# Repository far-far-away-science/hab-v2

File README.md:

# HAB Version II

Code and hardware designs for a high altitude balloon, the second version of https://github.com/far-far-away-science/hab . This version switches to a more efficient STM32L0 processor, adds support for a backup radio using LoRA, and hopes to include additional sensors.

Different licenses may apply to subsections of this repository. See the appropriate LICENSE files in the desired subdirectories.

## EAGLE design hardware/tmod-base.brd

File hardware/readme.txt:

all hardware designs, PCBs, schematics, drawings, specs go into this folder

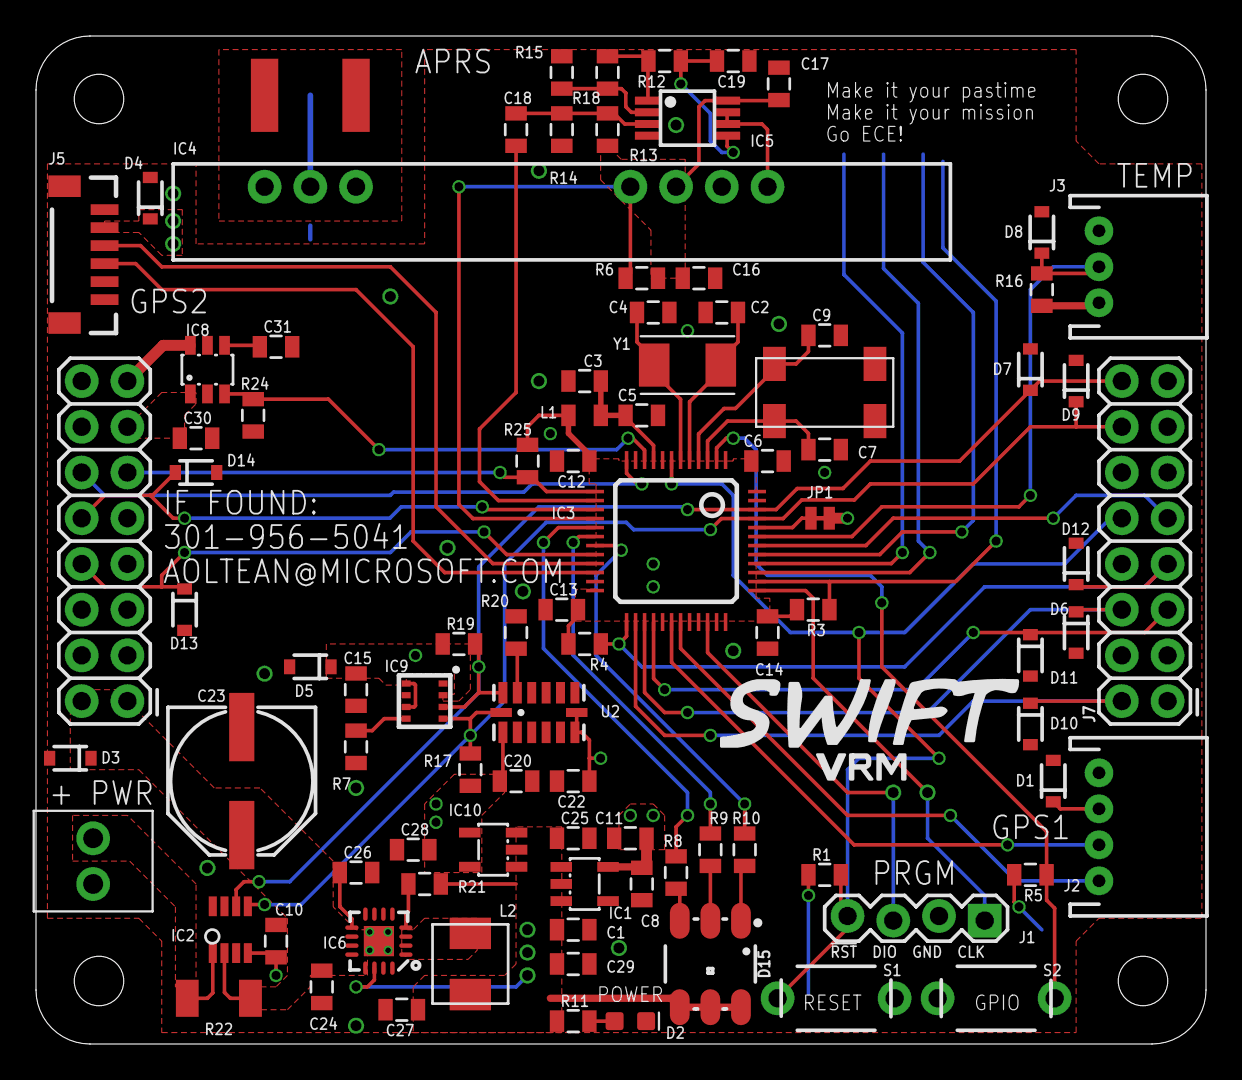
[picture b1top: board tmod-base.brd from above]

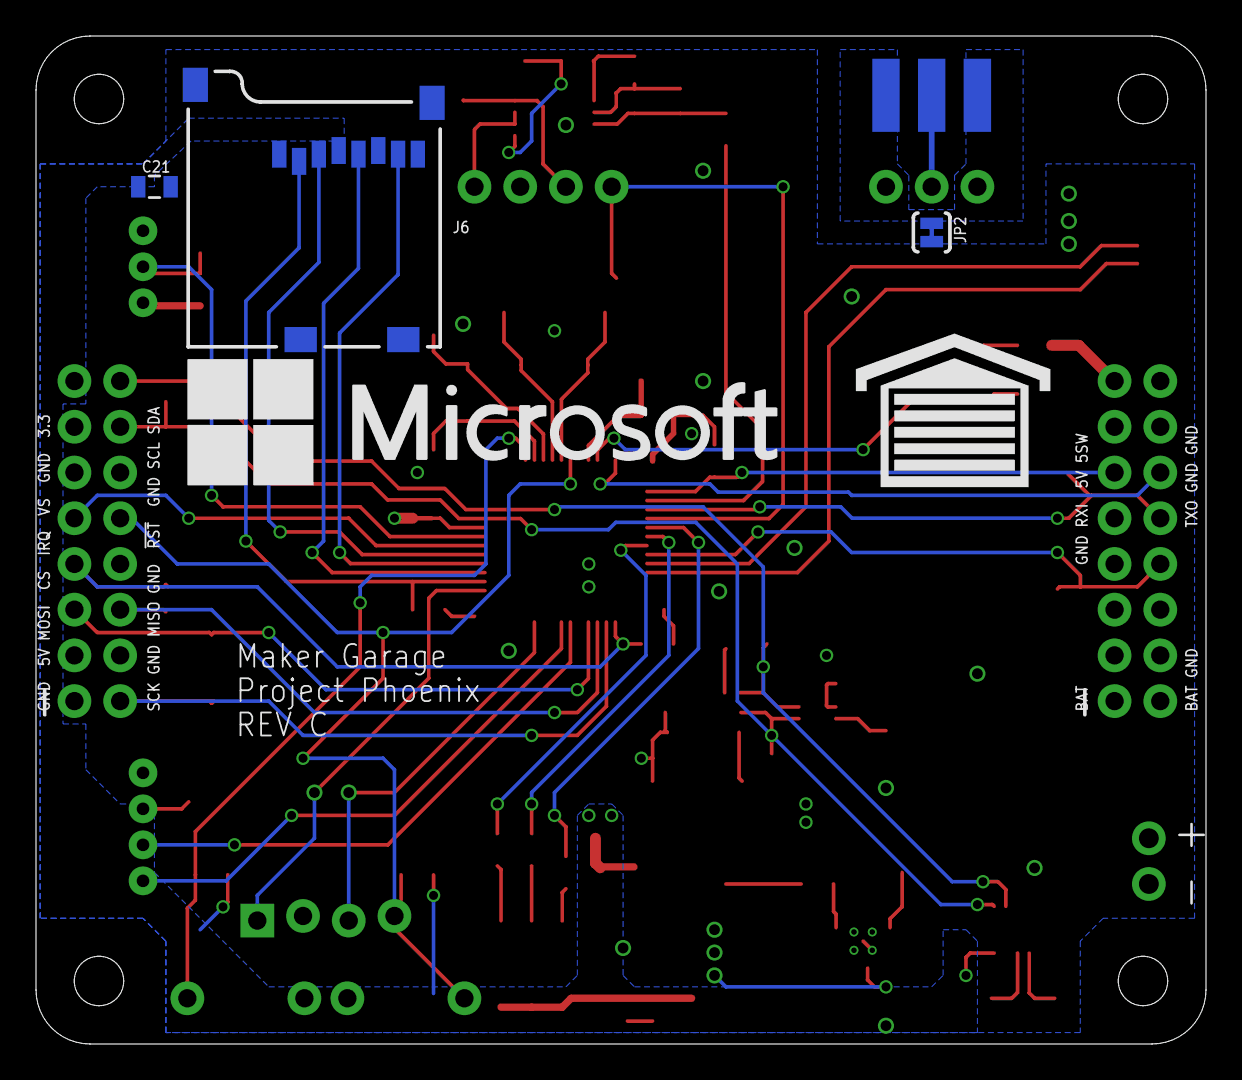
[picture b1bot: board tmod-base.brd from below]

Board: 4 copper layers, 65.0 x 56.0 mm, 100 parts (6 on the bottom side), 60 nets.

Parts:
C1, C5, C6, C10, C12, C13, C14, C15, C17, C22, C25, C30: 0.1u; 0805
C2, C4: 33p; 0805
C3, C8, C16, C21, C24, C28: 1u; 0805
C7, C9: 10p; 0805
C11, C27, C29: 10u; 0805
C18: 330p; 0805
C19: 100p; 0805
C20: 1.0u; 0805
C23: 150u; PANASONIC_E
C26: 3.3n; 0805
C31: 1n; 0805
D1, D4, D5, D6, D7, D8, D9, D10, D11, D12, D13, D14: 5.6V; SOD-323
D2: POWER; LED-0603
D3: 15V; SOD-323
D15: LED-RGB; LED-TRICOLOR-5050
FRAME1, FRAME2: FRAME-LETTERNO_PACKAGE; DUMMY
IC1, IC10: TPS70933; SOT23-DBV
IC2: INA219SOT; SOT23-8
IC3: STM32L443CCT6; TQFP48
IC4: HX1
IC5: LMP7702; VSSOP8
IC6: TPS62143; QFN16-3X3MM
IC8: TPS22918; SOT23-6L
IC9: BME280; BME280_LGA
J1: DNP; 1X04_LOCK@1
J2: GPS1; JST-4-PTH
J3: TEMP; JST-3-PTH
J4: POWER; 1X02_SCREW
J5: GPS2; 1X06-1MM
J6: MICRO-SD_CARD_SOCKET; MICRO-SD-SOCKET
J7: HAB-EXP
J$1: SMA_EDGE; SMA-EDGE
JP1: SMT-JUMPER_2_NC_TRACE_NO-SILK
JP2: GND; PAD-JUMPER-2-NC_BY_TRACE_YES_SILK
L1: FERRITE; 0805
L2: 2.2u; MPIA4012V2
R1, R3, R4, R5, R7, R20, R24, R25: 10K; 0805
R6, R16: 4.7K; 0805
R8, R9: 470; 0805
R10: 560; 0805
R11, R17, R19: 3.3K; 0805
R12: 330K; 0805
R13: 820K; 0805
R14: 220K; 0805
R15: 430K; 0805
R18: 680K; 0805
R21: 100K; 0805
R22: 0.01; 1210
S1: RST; TACTILE-PTH-THIN
S2: BTN; TACTILE-PTH-THIN
U2: ADXL345; LGA14
U$1: MSFT_LOGO
U$2: GARAGE
U$3: SWIFT
Y1: 8M; CRYSTAL-TXC-7A
Y2: 32768; ABS25

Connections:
3.3V: C6.1, C8.1, C10.1, C11.1, C12.1, C13.1, C14.1, C21.1, D1.C, IC1.5, IC2.4, IC3.1, IC3.24, IC3.36, IC3.48, J2.2, J6.VCC, J7.B15, L1.1, R1.2, R3.2, R4.2, R5.2, R25.2
5V: C1.1, C16.1, C17.1, C25.1, C27.1, C29.1, C30.1, D4.C, D15.4, D15.5, D15.6, IC1.1, IC4.5, IC5.8, IC6.14, IC8.1, IC10.1, J5.2, J7.A13, J7.B3, L2.2, R6.2, R11.1, R13.2, R21.2
5V_PI: IC8.6, J7.A15
!RST!: IC3.7, J1.4, J7.B10, R1.1, S1.2
A+: C18.2, IC5.3, R13.1, R14.2
A-: IC5.2, R15.2, R18.1
ADXL_SDO: R20.2, U2.12
BC: D15.1, R10.2
BME_SDO: IC9.P$5, R7.2
BOOT0: IC3.44, JP1.1
BTN: IC3.2, R5.1, S2.2
CT: C31.1, IC8.4
DAC: C18.1, IC3.14
GC: D15.2, R9.2
GND: C1.2, C2.2, C3.2, C4.2, C5.2, C6.2, C7.2, C8.2, C9.2, C10.2, C11.2, C12.2, C13.2, C14.2, C15.2, C16.2, C17.2, C19.2, C20.2, C21.2, C22.2, C23.-, C24.2, C25.2, C26.2, C27.2, C28.2, C29.2, C30.2, C31.2, D1.A, D2.C, D3.A, D4.A, D5.A, D6.A, D7.A, D8.A, D9.A, D10.A, D11.A, D12.A, D13.A, D14.A, IC1.2, IC2.3, IC2.7, IC2.8, IC3.8, IC3.23, IC3.35, IC3.47, IC4.6, IC5.4, IC6.5, IC6.6, IC6.7, IC6.8, IC6.15, IC6.16, IC6.EXT, IC8.2, IC9.P$1, IC9.P$7, IC10.2, J1.2, J2.1, J3.1, J4.2, J5.1, J5.5, J6.GND, J6.GND1, J6.GND3, J7.A4, J7.A9, J7.A14, J7.A16, J7.B1, J7.B4, J7.B8, J7.B12, J7.B13, JP1.2, JP2.2, R7.1, R14.1, R15.1, R20.1, R24.2, S1.1, S2.1, U2.2, U2.4, U2.5
GPSRX1: IC3.31, J2.4
GPSRX2: IC3.22, J5.4
GPSTX1: IC3.30, J2.3
GPSTX2: IC3.21, J5.3
HXEN: IC3.16, IC4.4, R6.1
K_PI: IC3.10, IC8.3, R24.1
LCS: D12.C, IC3.25, J7.B7, R4.1
LEDB: IC3.19, R10.1
LEDG: IC3.18, R9.1
LEDR: IC3.17, R8.1
LP1: IC5.1, R12.1, R18.2
LP2: C19.1, IC5.5, R12.2
MISO1: IC3.40, J6.DO
MISO2: D6.C, IC3.27, J7.B6
MOSI1: IC3.41, J6.DI
MOSI2: D11.C, IC3.28, J7.B5
OSC32_IN: C7.1, IC3.3, Y2.1
OSC32_OUT: C9.1, IC3.4, Y2.4
OSC_IN: C2.1, IC3.5, Y1.P$1
OSC_OUT: C4.1, IC3.6, Y1.P$2
PG5: IC6.4, R21.1
PLED: D2.A, R11.2
RC: D15.3, R8.2
RF_HX1: IC4.2, J$1.SIG
RGND: IC4.1, IC4.3, J$1.GND@0, J$1.GND@1, J$1.GND@2, J$1.GND@3, JP2.1
RSV5: D13.C, IC3.20, J7.A8
RSV6: D14.C, IC3.15, J7.A10
RSV7: IC3.42, J7.B9
R_RX: IC3.13, J7.A11, R25.1
R_TX: IC3.12, J7.A12
SCK1: IC3.39, J6.SCLK
SCK2: D10.C, IC3.26, J7.B2
SCL: D9.C, IC2.5, IC3.45, IC9.P$4, J7.B14, R17.1, U2.14
SDA: D7.C, IC2.6, IC3.46, IC9.P$3, J7.B16, R19.1, U2.13
SDCS: IC3.38, J6.CS, R3.1
SS5: C26.1, IC6.9
SW5: IC6.1, IC6.2, IC6.3, L2.1
SWCLK: IC3.37, J1.1
SWDIO: IC3.34, J1.3
TEMP: D8.C, IC3.43, J3.2, R16.1
TXD: IC4.7, IC5.6, IC5.7
VBAT: C23.+, C24.1, D3.C, IC2.2, IC6.10, IC6.11, IC6.12, IC6.13, J7.A1, J7.A2, R22.1
VDDA: C3.1, C5.1, IC3.9, L1.2
VIN: IC2.1, J4.1, R22.2
VS: C15.1, C20.1, C22.1, C28.1, D5.C, IC9.P$2, IC9.P$6, IC9.P$8, IC10.5, J3.3, J7.B11, R16.2, R17.2, R19.2, U2.1, U2.6, U2.7

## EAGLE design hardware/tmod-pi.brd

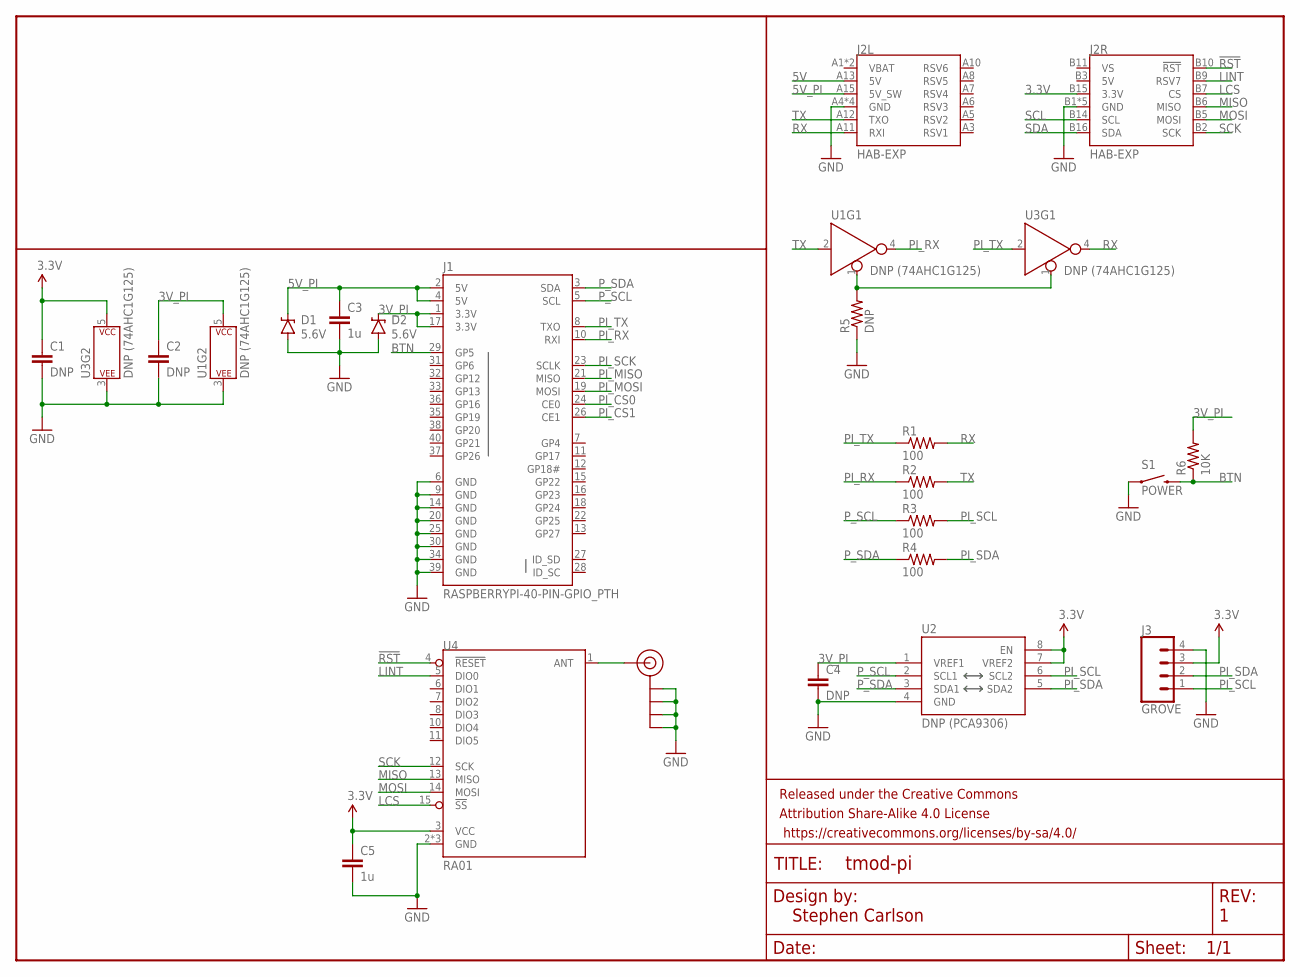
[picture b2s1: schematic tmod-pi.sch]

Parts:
C1, C2, C4: DNP; 0805
C3, C5: 1u; 0805
D1, D2: 5.6V; SOD-323
FRAME1: FRAME-LETTERNO_PACKAGE; DUMMY
J1: RASPBERRYPI-40-PIN-GPIO_PTH; 2X20_SHROUDED
J2: HAB-EXP
J3: GROVE; JST-4-PTH
J4: SMA_EDGE; SMA-EDGE
R1, R2, R3, R4: 100; 0805
R5: DNP; 0805
R6: 10K; 0805
S1: POWER; TACTILE-PTH-THIN
U1, U3: DNP (74AHC1G125); SOT23-5
U2: DNP (PCA9306); PCA9306DC
U4: RA01

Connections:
3.3V: C1.1, C5.1, J2.B15 (3.3V), J3.3, U2.7 (VREF2), U2.8 (EN), U3.5 (P$V+), U4.3 (VCC)
3V_PI: C2.1, C4.1, D2.C, J1.1 (3.3V), J1.17 (3.3V), R6.2, U1.5 (P$V+), U2.1 (VREF1)
5V: J2.A13 (5V), J2.B3 (5V)
5V_PI: C3.1, D1.C, J1.2 (5V), J1.4 (5V), J2.A15 (5V_SW)
!RST!: J2.B10 (!RST!), U4.4 (!RESET!)
ANT: J4.SIG (SIGNAL), U4.1 (ANT)
BTN: J1.29 (GP5), R6.1, S1.2
GND: C1.2, C2.2, C3.2, C4.2, C5.2, D1.A, D2.A, J1.6 (GND), J1.9 (GND), J1.14 (GND), J1.20 (GND), J1.25 (GND), J1.30 (GND), J1.34 (GND), J1.39 (GND), J2.A4 (GND), J2.A9 (GND), J2.A14 (GND), J2.A16 (GND), J2.B1 (GND), J2.B4 (GND), J2.B8 (GND), J2.B12 (GND), J2.B13 (GND), J3.4, J4.GND@0 (GND), J4.GND@1 (GND), J4.GND@2 (GND), J4.GND@3 (GND), R5.1, S1.1, U1.3 (P$V-), U2.4 (GND), U3.3 (P$V-), U4.2 (GND), U4.9 (GND), U4.16 (GND)
LCS: J2.B7 (CS), U4.15 (!SS!)
LINT: J2.B9 (RSV7), U4.5 (DIO0)
MISO: J2.B6 (MISO), U4.13 (MISO)
MOSI: J2.B5 (MOSI), U4.14 (MOSI)
PI_CS0: J1.24 (CE0)
PI_CS1: J1.26 (CE1)
PI_MISO: J1.21 (MISO)
PI_MOSI: J1.19 (MOSI)
PI_RX: J1.10 (RXI), R2.1, U1.4 (Y)
PI_SCK: J1.23 (SCLK)
PI_SCL: J3.1, R3.2, U2.6 (SCL2)
PI_SDA: J3.2, R4.2, U2.5 (SDA2)
PI_TX: J1.8 (TXO), R1.1, U3.2 (A)
P_SCL: J1.5 (SCL), R3.1, U2.2 (SCL1)
P_SDA: J1.3 (SDA), R4.1, U2.3 (SDA1)
RX: J2.A11 (RXI), R1.2, U3.4 (Y)
SCK: J2.B2 (SCK), U4.12 (SCK)
SCL: J2.B14 (SCL)
SDA: J2.B16 (SDA)
TX: J2.A12 (TXO), R2.2, U1.2 (A)
UART_EN: R5.2, U1.1 (!EN), U3.1 (!EN)
VBAT: J2.A1 (VBAT), J2.A2 (VBAT)
VS: J2.B11 (VS)

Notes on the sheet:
Stephen Carlson

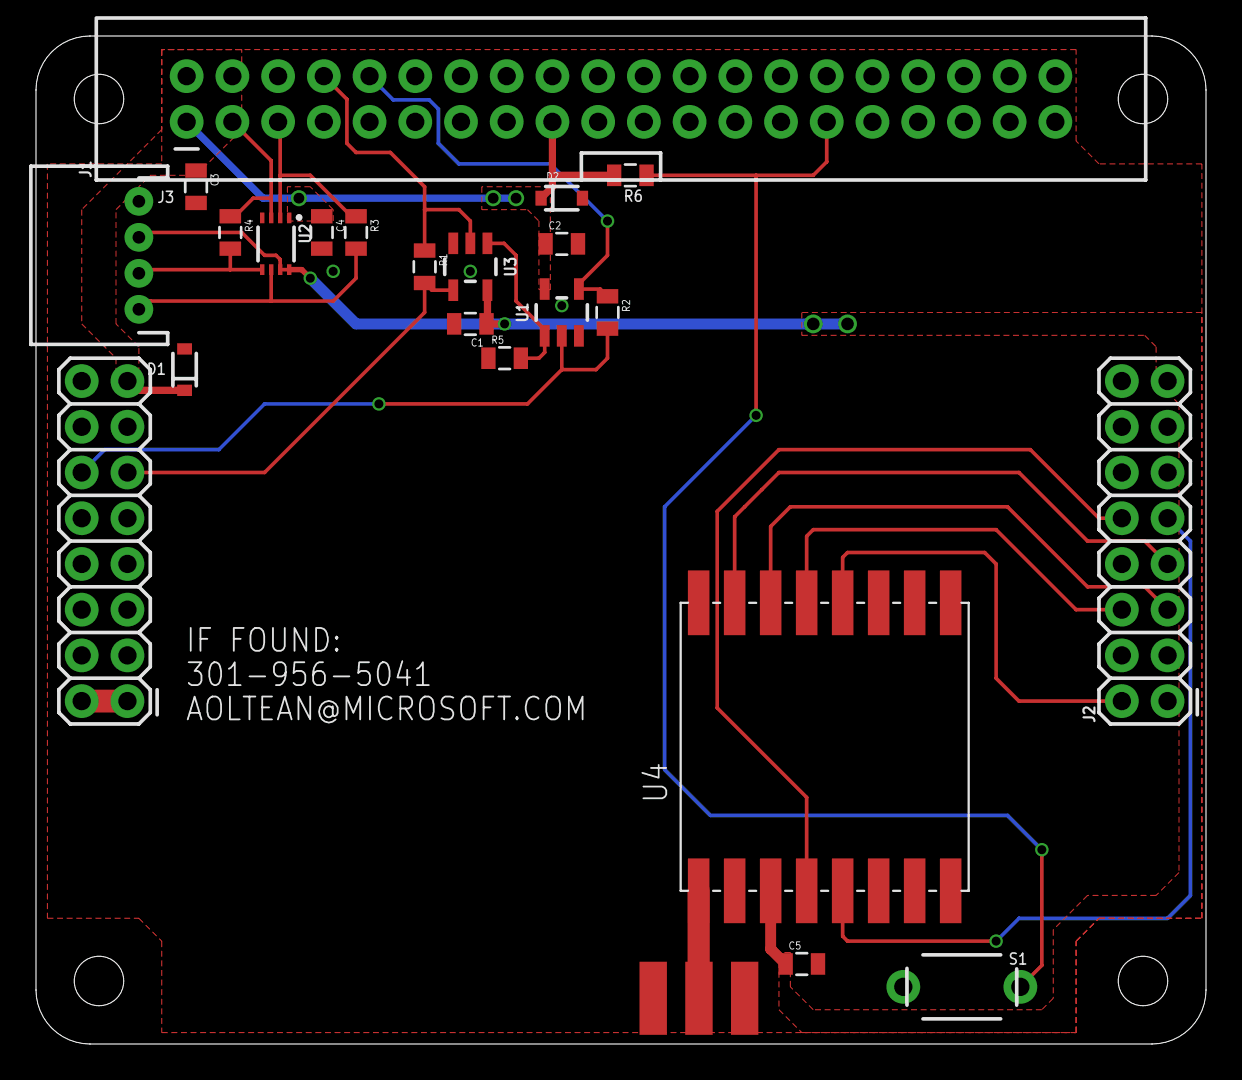
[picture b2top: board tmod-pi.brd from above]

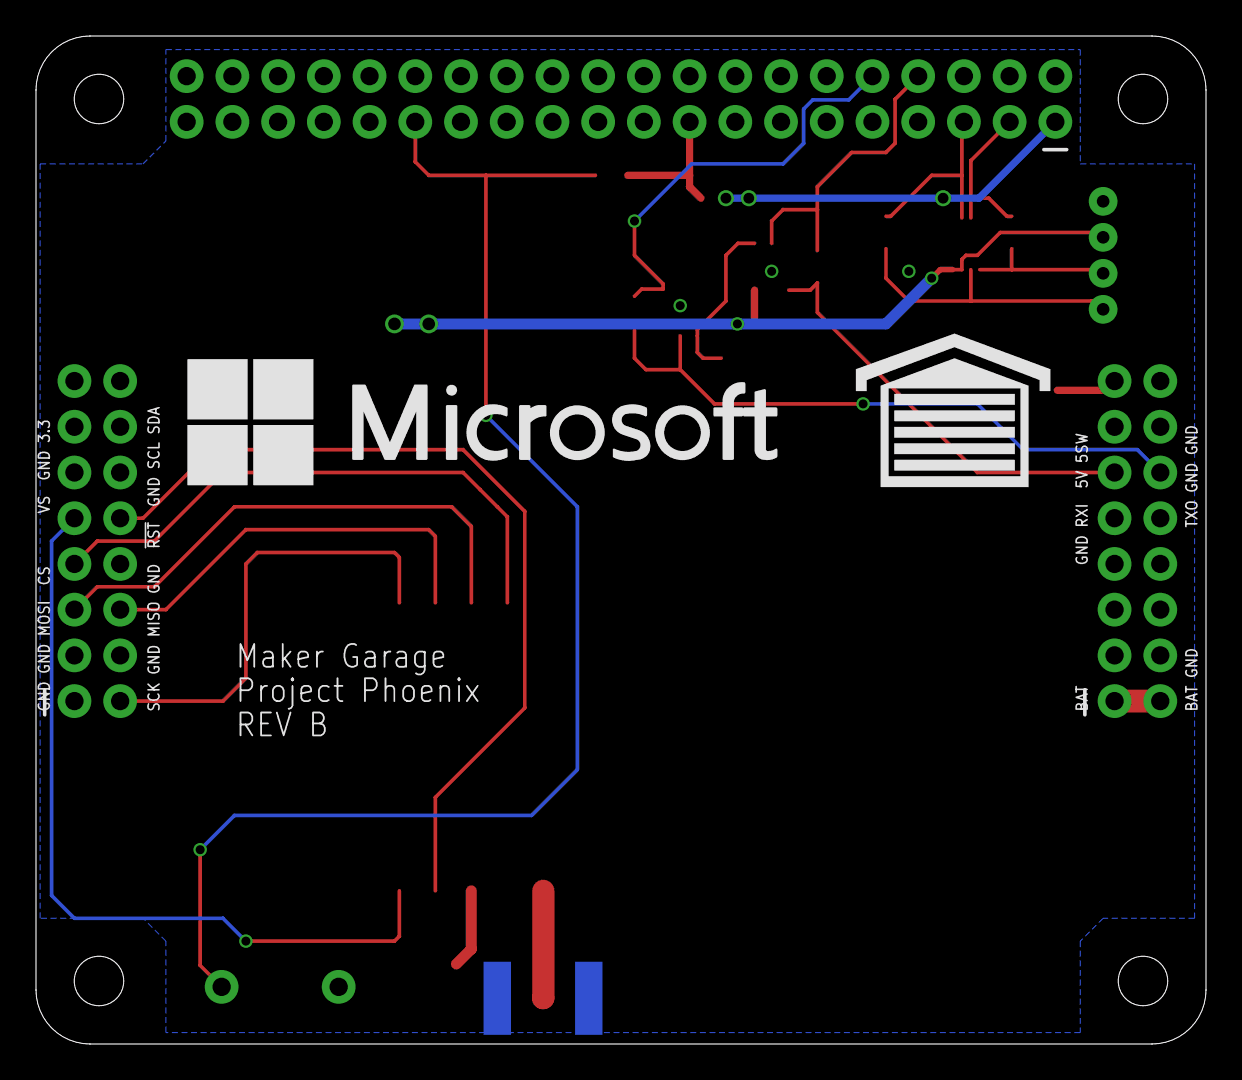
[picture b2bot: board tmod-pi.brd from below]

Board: 2 copper layers, 65.0 x 56.0 mm, 25 parts (2 on the bottom side), 23 nets.

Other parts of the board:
U$1: MSFT_LOGO
U$2: GARAGE

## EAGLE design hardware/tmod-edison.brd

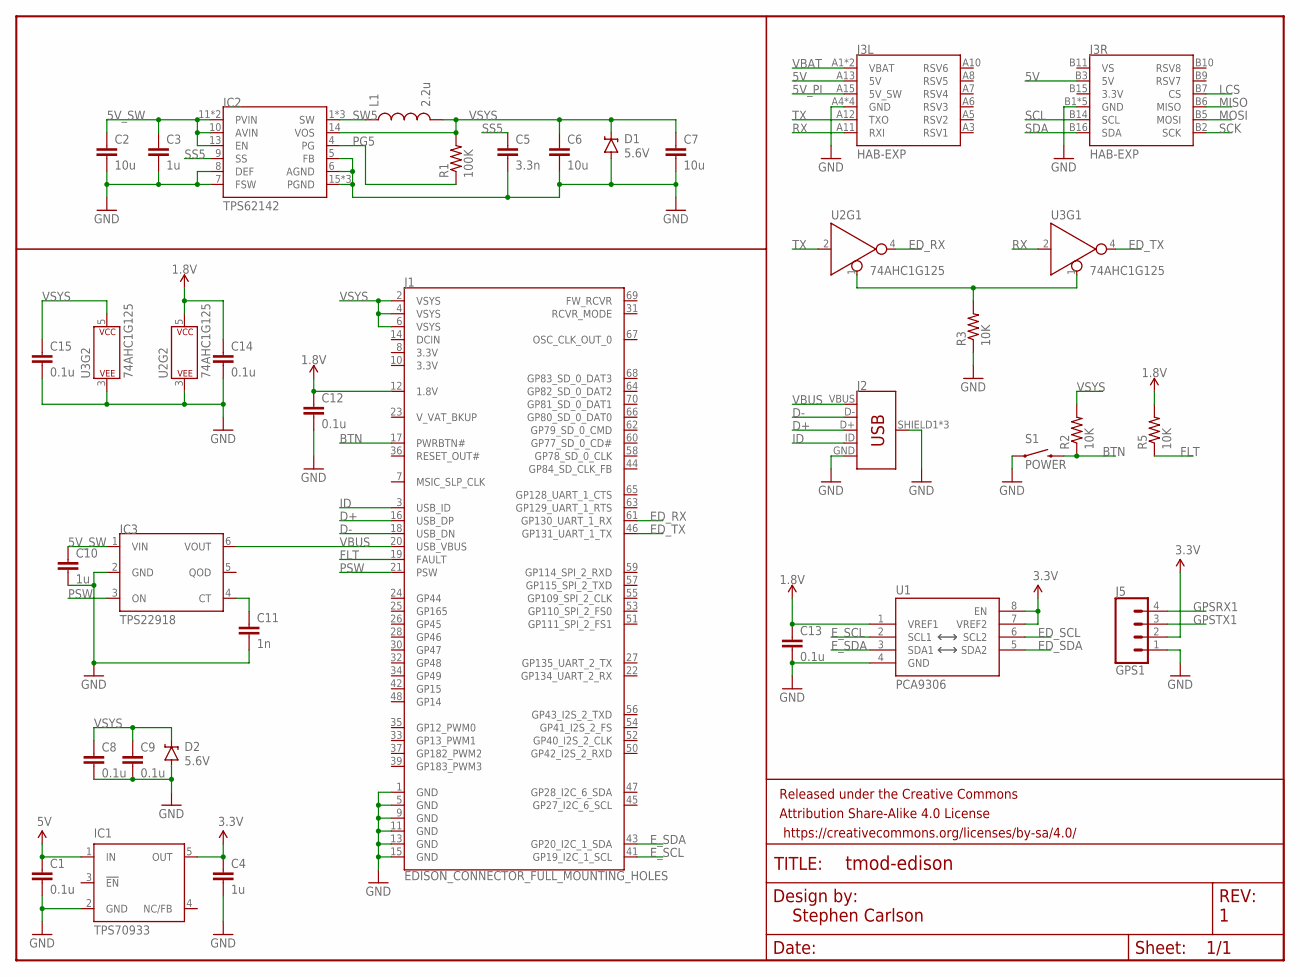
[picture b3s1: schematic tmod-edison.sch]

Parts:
C1, C8, C9, C12, C13, C14, C15: 0.1u; 0805
C2, C6, C7: 10u; 0805
C3, C4, C10: 1u; 0805
C5: 3.3n; 0805
C11: 1n; 0805
D1, D2: 5.6V; SOD-323
FRAME1: FRAME-LETTERNO_PACKAGE; DUMMY
IC1: TPS70933; SOT23-DBV
IC2: TPS62142; QFN16-3X3MM
IC3: TPS22918; SOT23-6L
J1: EDISON_CONNECTOR_FULL_MOUNTING_HOLES; EDISON_DAUGHTER
J2: USB_MICRO-B_FEMALE-SMT; USB-B-MICRO-SMD
J3: HAB-EXP
J5: GPS1; JST-4-PTH
L1: 2.2u; MPIA4012V2
R1: 100K; 0805
R2, R3, R5: 10K; 0805
S1: POWER; TACTILE-PTH-THIN
U1: PCA9306; PCA9306DC
U2, U3: 74AHC1G125; SOT23-5

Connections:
1.8V: C12.1, C13.1, C14.1, J1.12 (1.8V), R5.2, U1.1 (VREF1), U2.5 (P$V+)
3.3V: C4.1, IC1.5 (OUT), J3.B15 (3.3V), J5.2, U1.7 (VREF2), U1.8 (EN)
5V: C1.1, IC1.1 (IN), J3.A13 (5V), J3.B3 (5V)
5V_PI: J3.A15 (5V_SW)
5V_SW: C2.1, C3.1, C10.1, IC2.10 (AVIN), IC2.11 (PVIN), IC2.12 (PVIN), IC2.13 (EN), IC3.1 (VIN)
BTN: J1.17 (PWRBTN#), R2.1, S1.2
CT: C11.1, IC3.4 (CT)
D+: J1.16 (USB_DP), J2.D+
D-: J1.18 (USB_DN), J2.D-
ED_RX: J1.61 (GP130_UART_1_RX), U2.4 (Y)
ED_SCL: U1.6 (SCL2)
ED_SDA: U1.5 (SDA2)
ED_TX: J1.46 (GP131_UART_1_TX), U3.4 (Y)
E_SCL: J1.41 (GP19_I2C_1_SCL), U1.2 (SCL1)
E_SDA: J1.43 (GP20_I2C_1_SDA), U1.3 (SDA1)
FLT: J1.19 (FAULT), R5.1
GND: C1.2, C2.2, C3.2, C4.2, C5.2, C6.2, C7.2, C8.2, C9.2, C10.2, C11.2, C12.2, C13.2, C14.2, C15.2, D1.A, D2.A, IC1.2 (GND), IC2.5 (FB), IC2.6 (AGND), IC2.7 (FSW), IC2.8 (DEF), IC2.15 (PGND), IC2.16 (PGND), IC2.EXT (PGND), IC3.2 (GND), J1.1 (GND), J1.5 (GND), J1.9 (GND), J1.11 (GND), J1.13 (GND), J1.15 (GND), J2.GND, J2.SHIELD1 (SHIELD), J2.SHIELD2 (SHIELD), J2.SHIELD3 (SHIELD), J3.A4 (GND), J3.A9 (GND), J3.A14 (GND), J3.A16 (GND), J3.B1 (GND), J3.B4 (GND), J3.B8 (GND), J3.B12 (GND), J3.B13 (GND), J5.1, R3.1, S1.1, U1.4 (GND), U2.3 (P$V-), U3.3 (P$V-)
GPSRX1: J5.4
GPSTX1: J5.3
ID: J1.3 (USB_ID), J2.ID
LCS: J3.B7 (CS)
MISO: J3.B6 (MISO)
MOSI: J3.B5 (MOSI)
PG5: IC2.4 (PG), R1.1
PSW: IC3.3 (ON), J1.21 (PSW)
RX: J3.A11 (RXI), U3.2 (A)
SCK: J3.B2 (SCK)
SCL: J3.B14 (SCL)
SDA: J3.B16 (SDA)
SS5: C5.1, IC2.9 (SS)
SW5: IC2.1 (SW), IC2.2 (SW), IC2.3 (SW), L1.1
TX: J3.A12 (TXO), U2.2 (A)
UART_EN: R3.2, U2.1 (!EN), U3.1 (!EN)
VBAT: J3.A1 (VBAT), J3.A2 (VBAT)
VBUS: IC3.6 (VOUT), J1.20 (USB_VBUS), J2.VBUS
VS: J3.B11 (VS)
VSYS: C6.1, C7.1, C8.1, C9.1, C15.1, D1.C, D2.C, IC2.14 (VOS), J1.2 (VSYS), J1.4 (VSYS), J1.6 (VSYS), L1.2, R1.2, R2.2, U3.5 (P$V+)

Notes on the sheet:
Stephen Carlson

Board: 2 copper layers, 36 parts (2 on the bottom side), 25 nets, no tracks yet.

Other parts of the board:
U$1: MSFT_LOGO
U$2: GARAGE

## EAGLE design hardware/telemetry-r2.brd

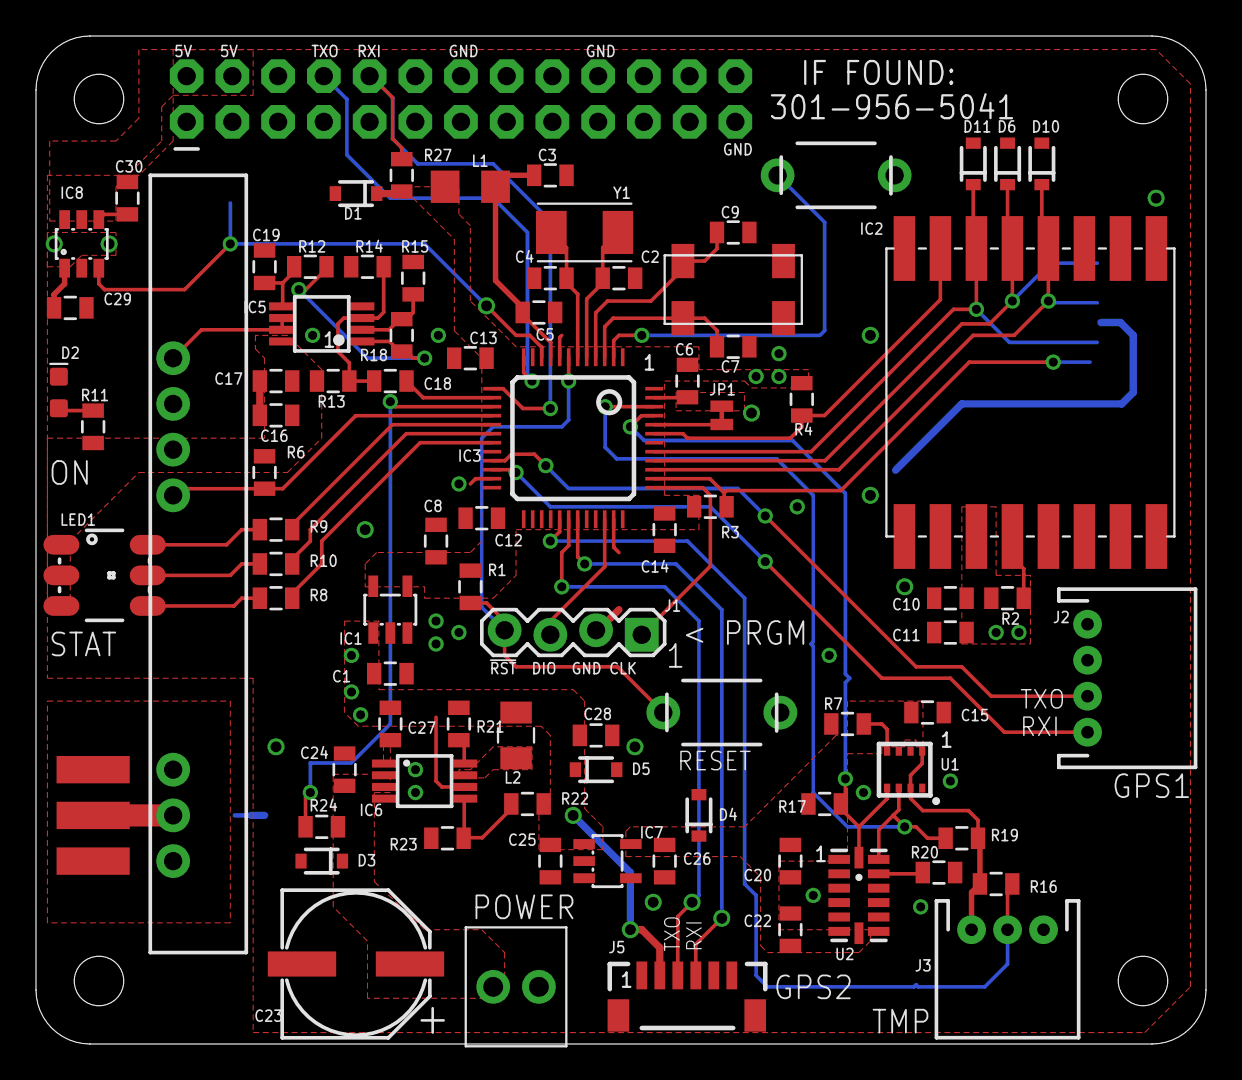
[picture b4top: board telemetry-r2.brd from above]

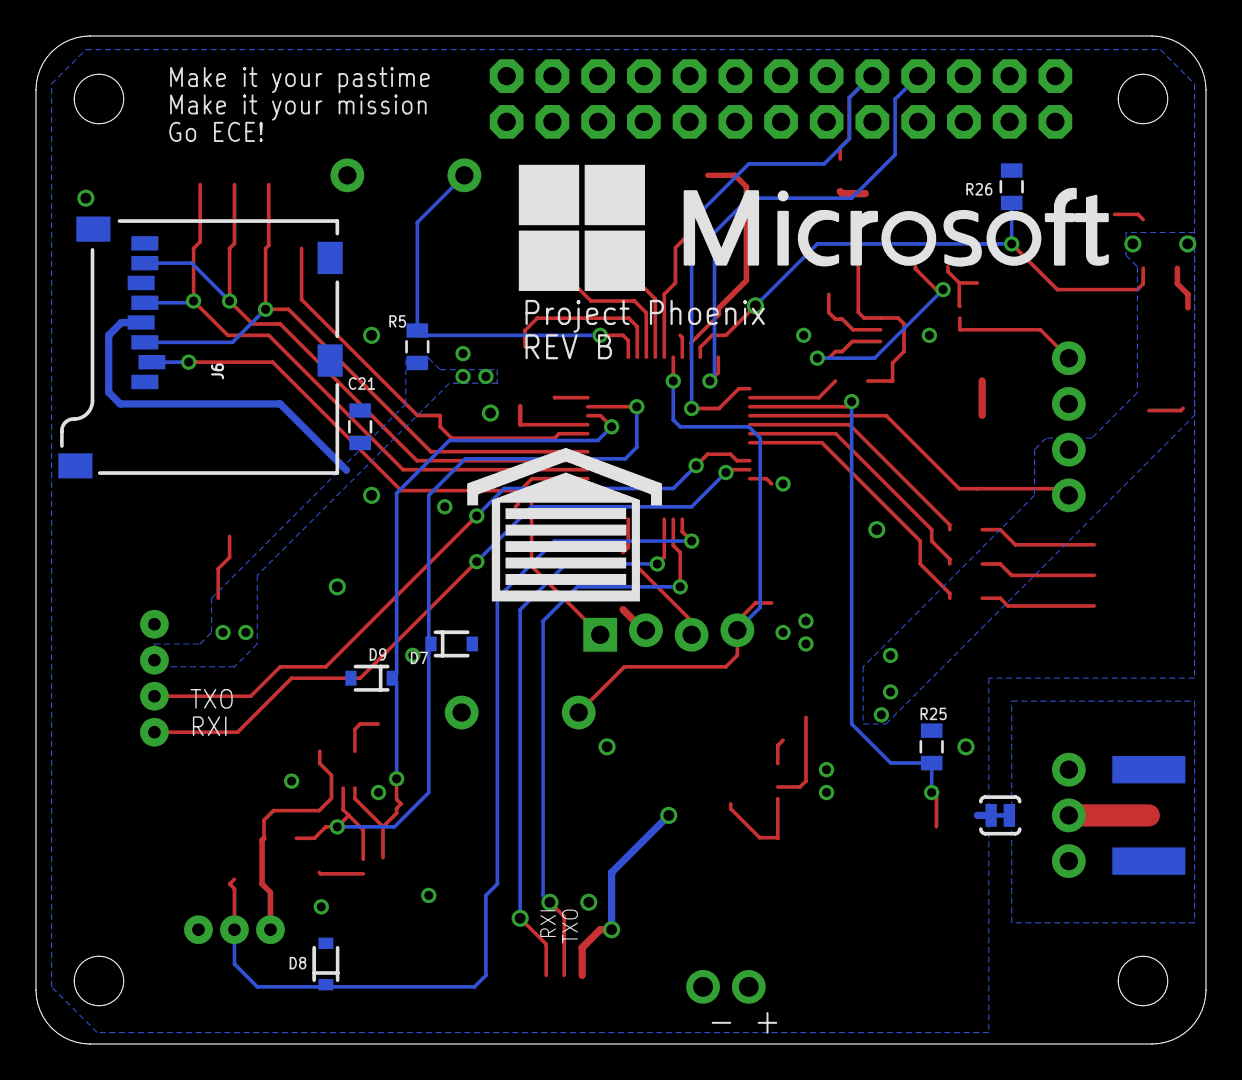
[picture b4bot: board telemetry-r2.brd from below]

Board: 2 copper layers, 65.0 x 56.0 mm, 99 parts (11 on the bottom side), 55 nets.

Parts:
C1, C5, C6, C10, C12, C13, C14, C15, C17, C22, C25, C29: 0.1u; 0805
C2, C4: 33p; 0805
C3, C8, C16, C21, C24, C26: 1u; 0805
C7, C9: 10p; 0805
C11, C27, C28: 10u; 0805
C18: 330p; 0805
C19: 100p; 0805
C20: 1.0u; 0805
C23: 100u; PANASONIC_E
C30: 1n; 0805
D1, D4, D5, D6, D7, D8, D9, D10, D11: 5.6V; SOD-323
D2: GREEN; LED-0603
D3: 15V; SOD-323
FRAME1, FRAME2: FRAME-LETTERNO_PACKAGE; DUMMY
IC1, IC7: TPS70933; SOT23-DBV
IC2: RA02
IC3: STM32L052C8T6; TQFP48
IC4: HX1
IC5: LMP7702; VSSOP8
IC6: TPS62160; MSOP8
IC8: TPS22918; SOT23-6L
J1: DNP; 1X04_LOCK@1
J2: GPS1; JST-4-PTH
J3: TEMP; JST-3-PTH
J4: POWER; 1X02_SCREW
J5: GPS2; 1X06-1MM
J6: MICRO-SD_CARD_SOCKET; MICRO-SD-SOCKET
J7: RASPBERRYPI-GPIO; 2X13-PI
J$1: SMA_EDGE; SMA-EDGE
JP1: SMT-JUMPER_2_NC_TRACE_NO-SILK
JP2: GND; PAD-JUMPER-2-NC_BY_TRACE_YES_SILK
L1: FERRITE; 1206
L2: 2.2u; 1008
LED1: COM-10866; LED-TRICOLOR-5050
R1, R2, R3, R4, R5, R7, R20, R21, R26, R27: 10K; 0805
R6, R16: 4.7K; 0805
R8, R9: 470; 0805
R10: 560; 0805
R11, R17, R19: 3.3K; 0805
R12: 330K; 0805
R13: 820K; 0805
R14: 220K; 0805
R15, R22, R24: 430K; 0805
R18: 680K; 0805
R23: 82K; 0805
R25: 100K; 0805
S1: RST; TACTILE-PTH-THIN
S2: BTN; TACTILE-PTH-THIN
U1: BME280; BME280_LGA
U2: ADXL345; LGA14
U$1: GARAGE
U$2: MSFT_LOGO
Y1: 8M; CRYSTAL-TXC-7A
Y2: 32768; ABS25

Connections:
3.3V: C6.1, C8.1, C10.1, C11.1, C12.1, C13.1, C14.1, C21.1, D1.C, IC1.5, IC2.3, IC3.1, IC3.24, IC3.36, IC3.48, J2.2, J6.VCC, L1.1, R1.2, R2.2, R3.2, R4.2, R5.2, R27.2
5V: C1.1, C16.1, C17.1, C25.1, C27.1, C28.1, C29.1, D5.C, IC1.1, IC4.5, IC5.8, IC6.6, IC7.1, IC8.1, J5.2, L2.2, LED1.1, LED1.2, LED1.3, R6.2, R11.1, R13.2, R21.2, R22.2
5V_PI: IC8.6, J7.2, J7.4
!LORA_RST!: IC2.4, R2.1
!RST!: IC3.7, J1.4, R1.1, S1.2
A+: C18.2, IC5.3, R13.1, R14.2
A-: IC5.2, R15.2, R18.1
ADXL_SDO: R20.2, U2.12
BC: LED1.4, R8.2
BME_SDO: R7.2, U1.P$5
BOOT0: IC3.44, JP1.1
BTN: IC3.2, R5.1, S2.2
CT: C30.1, IC8.4
DAC: C18.1, IC3.14
FB5: IC6.5, R22.1, R23.2
GC: LED1.6, R9.2
GND: C1.2, C2.2, C3.2, C4.2, C5.2, C6.2, C7.2, C8.2, C9.2, C10.2, C11.2, C12.2, C13.2, C14.2, C15.2, C16.2, C17.2, C19.2, C20.2, C21.2, C22.2, C23.-, C24.2, C25.2, C26.2, C27.2, C28.2, C29.2, C30.2, D1.A, D2.C, D3.A, D4.A, D5.A, D6.A, D7.A, D8.A, D9.A, D10.A, D11.A, IC1.2, IC1.4, IC2.1, IC2.2, IC2.9, IC2.16, IC3.8, IC3.23, IC3.35, IC3.47, IC4.6, IC5.4, IC6.1, IC6.4, IC7.2, IC8.2, J1.2, J2.1, J3.1, J4.2, J5.1, J5.5, J6.GND, J6.GND1, J6.GND3, J7.6, J7.9, J7.14, J7.20, J7.25, JP1.2, JP2.2, R7.1, R14.1, R15.1, R20.1, R23.1, R25.1, R26.2, S1.1, S2.1, U1.P$1, U1.P$7, U2.2, U2.4, U2.5
GPSRX1: IC3.22, J2.4
GPSRX2: IC3.31, J5.4
GPSTX1: IC3.21, J2.3
GPSTX2: IC3.30, J5.3
HXEN: IC3.16, IC4.4, R6.1
K_PI: IC3.10, IC8.3, R26.1
LCS: IC2.15, IC3.43, R4.1
LEDB: IC3.19, R8.1
LEDG: IC3.17, R9.1
LEDR: IC3.18, R10.1
LP1: IC5.1, R12.1, R18.2
LP2: C19.1, IC5.5, R12.2
MISO: D6.C, IC2.13, IC3.40, J6.DO
MOSI: D11.C, IC2.14, IC3.41, J6.DI
OSC32_IN: C7.1, IC3.3, Y2.1
OSC32_OUT: C9.1, IC3.4, Y2.4
OSC_IN: C2.1, IC3.5, Y1.P$1
OSC_OUT: C4.1, IC3.6, Y1.P$2
PG5: IC6.8, R21.1
PLED: D2.A, R11.2
RC: LED1.5, R10.2
RF_HX1: IC4.2, J$1.SIG
RGND: IC4.1, IC4.3, J$1.GND@0, J$1.GND@1, J$1.GND@2, J$1.GND@3, JP2.1
R_RX: IC3.13, J7.10, R27.1
R_TX: IC3.12, J7.8
SCK: D10.C, IC2.12, IC3.39, J6.SCLK
SCL: D9.C, IC3.45, R17.1, U1.P$4, U2.14
SDA: D7.C, IC3.46, R19.1, U1.P$3, U2.13
SDCS: IC3.38, J6.CS, R3.1
SW5: IC6.7, L2.1
SWCLK: IC3.37, J1.1
SWDIO: IC3.34, J1.3
TEMP: D8.C, IC3.29, J3.2, R16.1
TXD: IC4.7, IC5.6, IC5.7
VBAT: C23.+, C24.1, D3.C, IC6.2, IC6.3, J4.1, R24.2
VDDA: C3.1, C5.1, IC3.9, L1.2
VDIV: IC3.15, R24.1, R25.2
VS: C15.1, C20.1, C22.1, C26.1, D4.C, IC7.5, J3.3, R16.2, R17.2, R19.2, U1.P$2, U1.P$6, U1.P$8, U2.1, U2.6, U2.7

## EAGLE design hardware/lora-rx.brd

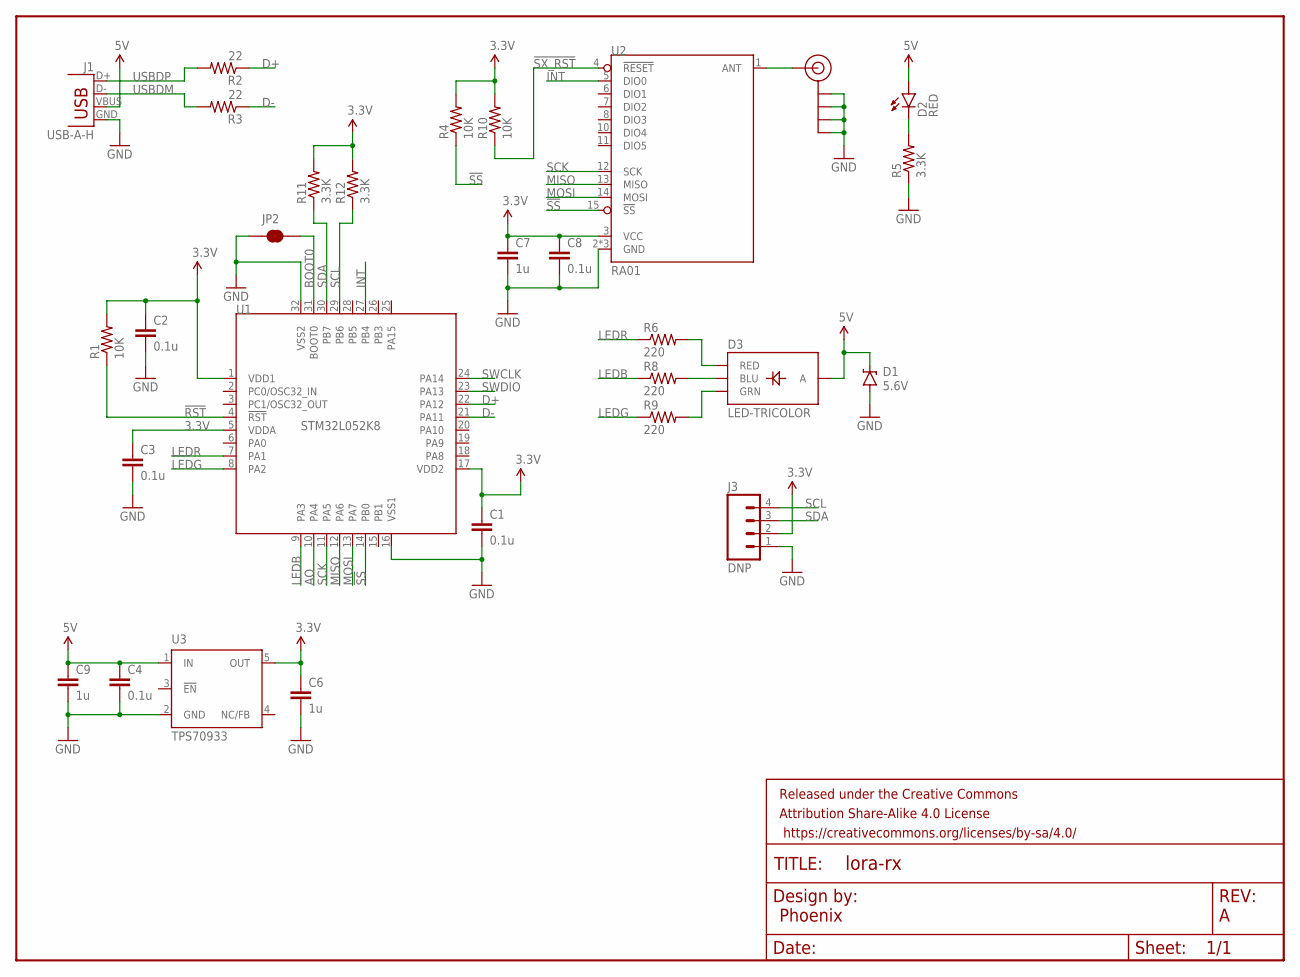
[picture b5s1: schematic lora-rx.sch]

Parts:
C1, C2, C3, C4, C8: 0.1u; 0805
C6, C7, C9: 1u; 0805
D1: 5.6V; SOD-323
D2: RED; LED-0603
D3: LED-TRICOLOR; LED-TRICOLOR-SMD
FRAME1: FRAME-LETTERNO_PACKAGE; DUMMY
J1: USB-A-H
J2: SMA_EDGE; SMA-EDGE
J3: DNP; 1X04-1.5MM_JST
JP2: JUMPER-SMT_2_NC_TRACE_NO-SILK; SMT-JUMPER_2_NC_TRACE_NO-SILK
R1, R4, R10: 10K; 0805
R2, R3: 22; 0805
R5, R11, R12: 3.3K; 0805
R6, R8, R9: 220; 0805
U1: STM32L052K8; TQFP32-08
U2: RA01
U3: TPS70933; SOT23-DBV

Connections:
3.3V: C1.1, C2.1, C3.1, C6.1, C7.1, C8.1, J3.2, R1.2, R4.2, R10.2, R11.2, R12.2, U1.1 (VDD1), U1.5 (VDDA), U1.17 (VDD2), U2.3 (VCC), U3.5 (OUT)
5V: C4.1, C9.1, D1.C, D2.A, D3.A, J1.VBUS, U3.1 (IN)
!RST!: R1.1, U1.4 (!RST!)
!SS!: R4.1, U1.14 (PB0), U2.15 (!SS!)
!SX_RST!: R10.1, U2.4 (!RESET!)
ANT: J2.SIG (SIGNAL), U2.1 (ANT)
AO: U1.10 (PA4)
BL: D3.B (BLU), R8.2
BOOT0: JP2.2, U1.31 (BOOT0)
D+: R2.1, U1.22 (PA12)
D-: R3.1, U1.21 (PA11)
GL: D3.G (GRN), R9.2
GND: C1.2, C2.2, C3.2, C4.2, C6.2, C7.2, C8.2, C9.2, D1.A, J1.GND, J2.GND@0 (GND), J2.GND@1 (GND), J2.GND@2 (GND), J2.GND@3 (GND), J3.1, JP2.1, R5.1, U1.16 (VSS1), U1.32 (VSS2), U2.2 (GND), U2.9 (GND), U2.16 (GND), U3.2 (GND)
INT: U1.27 (PB4), U2.5 (DIO0)
LEDB: R8.1, U1.9 (PA3)
LEDG: R9.1, U1.8 (PA2)
LEDR: R6.1, U1.7 (PA1)
MISO: U1.12 (PA6), U2.13 (MISO)
MOSI: U1.13 (PA7), U2.14 (MOSI)
PLED: D2.C, R5.2
RL: D3.R (RED), R6.2
SCK: U1.11 (PA5), U2.12 (SCK)
SCL: J3.4, R12.1, U1.29 (PB6)
SDA: J3.3, R11.1, U1.30 (PB7)
SWCLK: U1.24 (PA14)
SWDIO: U1.23 (PA13)
USBDM: J1.D-, R3.2
USBDP: J1.D+, R2.2

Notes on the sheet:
Phoenix

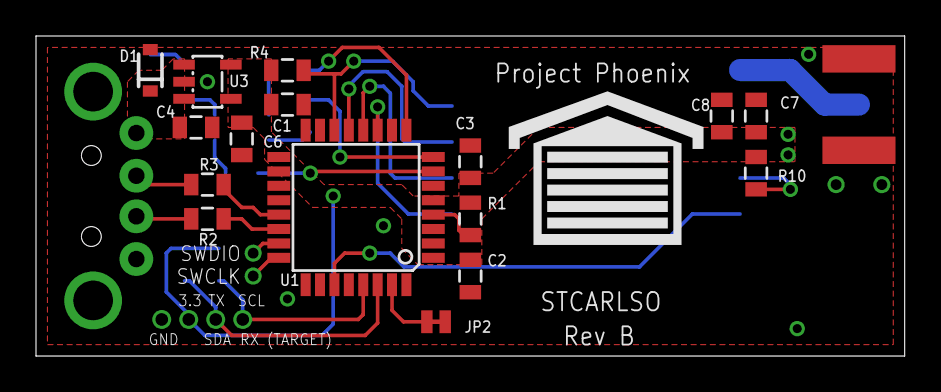
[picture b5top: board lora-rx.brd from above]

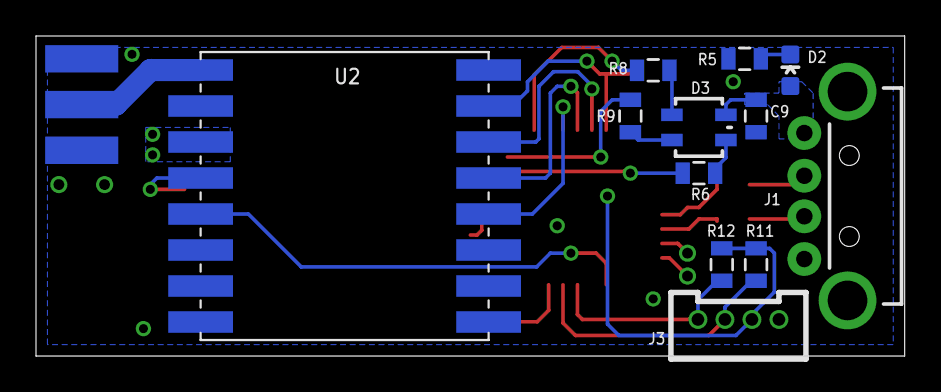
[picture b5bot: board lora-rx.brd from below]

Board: 2 copper layers, 48.3 x 17.8 mm, 31 parts (13 on the bottom side), 25 nets.

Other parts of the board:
U$1: GARAGE

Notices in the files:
parts and their libraries:
SparkFun-Passives: Licensing: Creative Commons ShareAlike 4.0 International - https://creativecommons.org/licenses/by-sa/4.0
SparkFun-Aesthetics: Released under the Creative Commons Attribution Share-Alike 4.0 License
SparkFun-Aesthetics: https://creativecommons.org/licenses/by-sa/4.0
